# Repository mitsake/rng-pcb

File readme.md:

# CircuitPython Random Number Generator

This is my contribution to the Boldport Club's community run Board Swap Project, a hardware random number generator that uses avalanche noise to make patterns and roll dice. Apart from being part of the community project, my other motivations were interest in randomness and the processes that can be used to generate it, along with the idea of using PCBs to build an enclosure.

**Please note that I made this for fun - if you need random numbers for anything important, this isn't the project you're looking for.**

## Operation

A ST662 charge pump produces the 12 V required to reverse-bias Q1, which produces the actual randomness. When electrons travel through this junction, Q2 allows current to flow to ground. This signal is amplified by Q3, run through a voltage divider, and fed into the ADC of an ATSAMD21E18 microcontroller, which has been flashed with the [Adafruit Trinket M0][trinket] bootloader to allow programming with CircuitPython.

[trinket]: https://www.adafruit.com/product/3500

The display is an inexpensive 128 × 32 SSD1306-based OLED, and the in-built capacitive touch that's on the Trinket M0 hardware is routed to the top left (pin A3) and right (A4) corners of the top PCB to allow for input. If you don't have KiCad, you can use the [PDF schematic][schematic] - it's all pretty simple.

[schematic]: docs/schematic.pdf

## Making your own

You can use the KiCad files in the 'hardware' directory to generate gerbers and get them made at your favourite PCB fab. I had my prototypes made at [OSH Park][oshpark] (who accept the `.kicad_pcb` file directly), and once I'd finished the final design, got a 'protopack' made at [Dirty PCBs][dirtypcbs]. The gerbers are available in a [zip file][zip] which should be accepted by most fabs, and assembly instructions can be found [here][assembly]. Make sure the PCB thickness is 1.6 mm - Dirty PCBs default to 1.2 mm, which will cause clearance issues.

[oshpark]: https://www.oshpark.com/
[dirtypcbs]: https://dirtypcbs.com/store/pcbs/
[assembly]: docs/assembly.md
[zip]: hardware/gerbers/rng-pcb-dirtypcbs.zip

## Credits

This project was only possible thanks to the electrical designs, libraries, and articles written by others. Many thanks to the people below whose work was used to build this project, and to the Boldport Club Discord for the inspiration to build something and the help and support they're always happy to provide.

- Adafruit's [Trinket M0 schematic][m0schem], which I shamelessly copied for the microcontroller and its supporting components. I've also used Adafruit's bootloader (and consequently their USB VID and PID), so this project is strictly a DIY build. Please don't distribute finished versions of this project with the Adafruit bootloader installed.
- Aaron Logue's [Hardware Random Number Generator][aaronl] started me on the path towards making the project, and gave the basic circuit.
- Giorgio Vazzana's [amazing writeup][giorgiov] of his experiments with this design, including precise measurements of transistor breakdown voltages, analogue and digital output circuits, and rigorous testing of the output.
- Walter Anderson's [Google Sites][waltera] page has a lot of really interesting information on entropy, both from this design and others.
- Rob Seward's [Arduino Uno design][robs] feeds the output from the noise circuit into an ADC and uses software to produce the actual random bits, an approach I mostly copied.
- The pattern on the top PCB (`triangle_pattern.kicad_mod`) is made with Quinn Rohlf's [Trianglify][trianglify] library.
- The `mouse-bite-2mm-slot.kicad_mod` footprint comes from [this repository][madworm] by madworm.

[m0schem]: https://learn.adafruit.com/assets/45723
[aaronl]: http://www.cryogenius.com/hardware/rng/
[giorgiov]: http://holdenc.altervista.org/avalanche/index.html
[waltera]: https://sites.google.com/site/astudyofentropy/project-definition/avalanche-noise
[robs]: http://robseward.com/misc/RNG2/
[trianglify]: https://github.com/qrohlf/trianglify
[madworm]: https://github.com/madworm/Panelization.pretty

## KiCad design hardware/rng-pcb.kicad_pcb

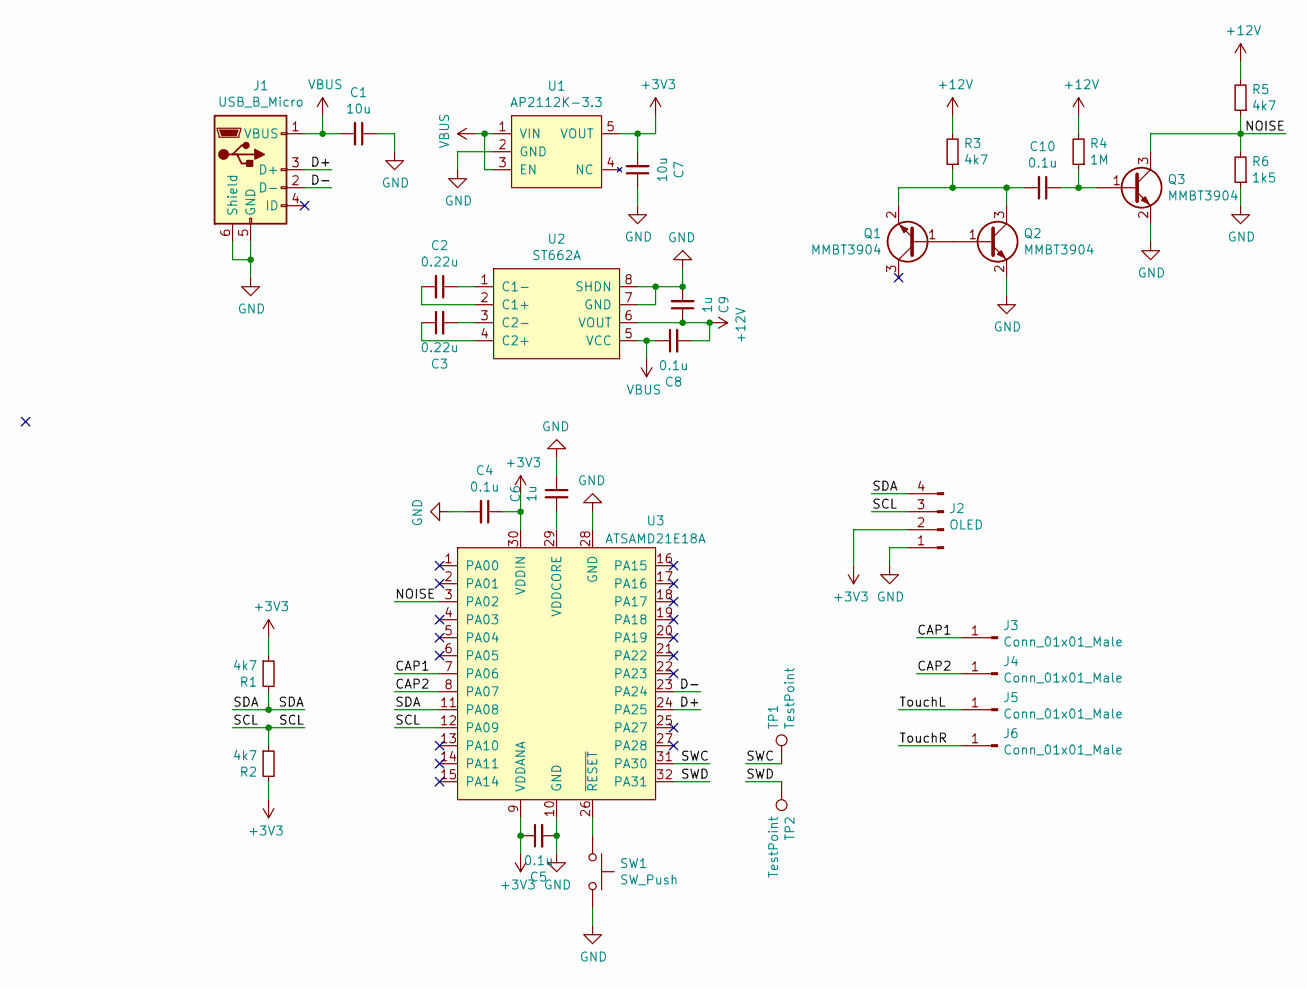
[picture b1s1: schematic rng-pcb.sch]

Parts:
C1, C7: 10u; C_0603
C2, C3: 0.22u; C_0603
C4, C5, C8, C10: 0.1u; C_0603
C6, C9: 1u; C_0603
J1: USB_B_Micro; Molex-476420001
J2: OLED; PinHeader_1x04_P2.54mm_Vertical
J3, J4, J5, J6: Conn_01x01_Male; TH_Pad
Q1, Q2, Q3: MMBT3904; SOT523
R1, R2, R3, R5: 4k7; R_0603
R4: 1M; R_0603
R6: 1k5; R_0603
SW1: SW_Push; Wurth-434331013822
TP1, TP2: TestPoint; Test_Point_Pad_d1.0mm
U1: AP2112K-3.3; TSOT-23-5
U2: ST662A; SOIC-8_3.9x4.9mm_Pitch1.27mm
U3: ATSAMD21E18A; TQFP-32_7x7mm_Pitch0.8mm

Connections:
+3V3: C4.1, C5.1, C7.2, J2.2, R1.1, R2.2, U1.5 (VOUT), U3.9 (VDDANA), U3.30 (VDDIN)
+12V: C8.2, C9.1, R3.2, R4.2, R5.2, U2.6 (VOUT)
/CAP1: J3.1, U3.7 (PA06)
/CAP2: J4.1, U3.8 (PA07)
/D+: J1.3 (D+), U3.24 (PA25)
/D-: J1.2 (D-), U3.23 (PA24)
/NOISE: Q3.3 (C), R5.1, R6.2, U3.3 (PA02)
/SCL: J2.3, R2.1, U3.12 (PA09)
/SDA: J2.4, R1.2, U3.11 (PA08)
/SWC: TP1.1, U3.31 (PA30)
/SWD: TP2.1, U3.32 (PA31)
/TouchL: J5.1
/TouchR: J6.1
GND: C1.1, C4.2, C5.2, C6.1, C7.1, C9.2, J1.5 (GND), J1.6 (Shield), J2.1, Q2.2 (E), Q3.2 (E), R6.1, SW1.2, U1.2 (GND), U2.7 (GND), U2.8 (SHDN), U3.10 (GND), U3.28 (GND)
unnamed: C2.1, U2.1 (C1-)
unnamed: C2.2, U2.2 (C1+)
unnamed: C3.1, U2.4 (C2+)
unnamed: C3.2, U2.3 (C2-)
unnamed: C6.2, U3.29 (VDDCORE)
unnamed: C10.1, Q3.1 (B), R4.1
unnamed: C10.2, Q1.2 (E), Q2.3 (C), R3.1
unnamed: Q1.1 (B), Q2.1 (B)
unnamed: SW1.1, U3.26 (~RESET)
VBUS: C1.2, C8.1, J1.1 (VBUS), U1.1 (VIN), U1.3 (EN), U2.5 (VCC)

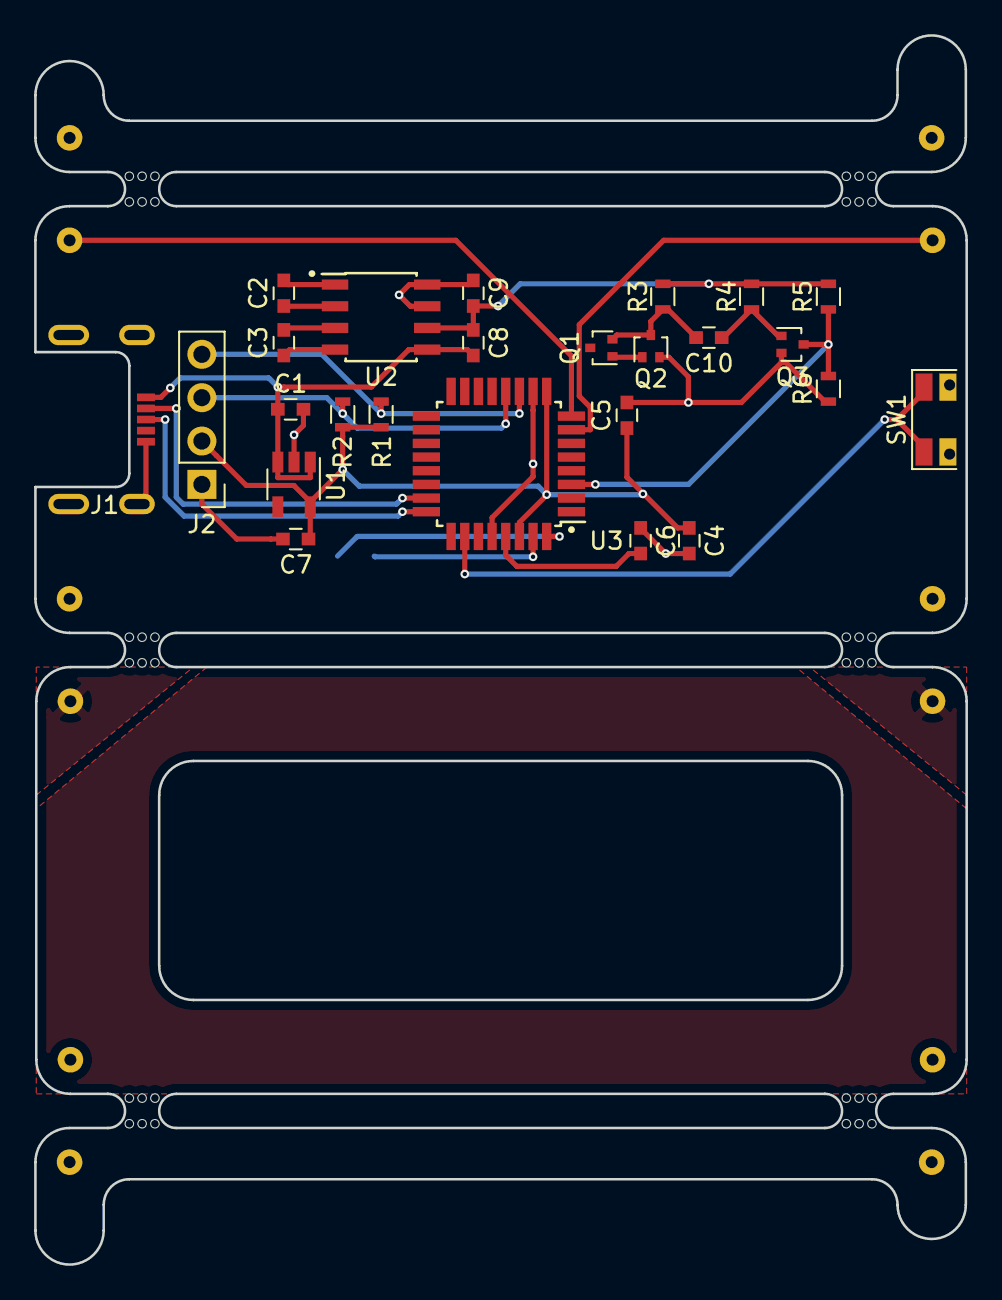
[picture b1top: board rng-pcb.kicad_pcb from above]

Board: 2 copper layers, 54.6 x 72.0 mm, 37 parts (0 on the bottom side), 22 nets.

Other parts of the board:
mouse-bite-2mm-slot, mouse-bite-2mm-slot#2, mouse-bite-2mm-slot#3, mouse-bite-2mm-slot#4, mouse-bite-2mm-slot#5, mouse-bite-2mm-slot#6: VAL**; mouse-bite-2mm-slot

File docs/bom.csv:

"Reference","Quantity","Value","Footprint","Digikey","Mouser"
"C1, C7",2,"10 μF, 16 V","0603","1276-6769-1-ND","81-GRM188C81C106MA3D"
"C2, C3",2,"0.22 μF, 16 V","0603","1276-1112-1-ND","81-GCJ188R71C224KA1D"
"C4, C5, C8, C10",4,"0.1 μF, 16 V","0603","1276-1005-1-ND","81-GCJ188R71C105KA1D"
"C6, C9",2,"1 μF, 16 V","0603","1276-6524-1-ND","81-GCM188R71C105KA4J"
"J1",1,"USB-micro jack","Molex 47642-0001","WM1398CT-ND","538-47642-0001"
"J2",1,"128 × 32 OLED","1×4 pin header","",""
"Q1, Q2, Q3",3,"MMBT3904T","SOT416 (aka SOT523)","MMBT3904T-FDICT-ND","621-MMBT3904T-F"
"R1, R2, R3, R5",4,"4.7 kΩ","0603","311-4.70KHRCT-ND","603-RC0603FR-074K7L"
"R4",1,"1 MΩ","0603","311-1.00MHRCT-ND","603-RC0603FR-071ML"
"R6",1,"1.5 kΩ","0603","311-1.50KHRCT-ND","603-RC0603FR-071K5L"
"SW1",1,"Push switch","Wurth 434331013822","732-10144-1-ND","710-434331013822"
"U1",1,"AP2112K-3.3","SOT 23-5","AP2112K-3.3TRG1DICT-ND","621-AP2112K-3.3TRG1"
"U2",1,"ST662A","SOIC-8","497-6541-1-ND","511-ST662ABD-TR"
"U3",1,"ATSAMD21E18A","TQFP-32","ATSAMD21E18A-AUTCT-ND","556-ATSAMD21E18A-AUT"

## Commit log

2019-11-18 Directory restructure and image testing
2019-11-20 Added another picture
2019-11-24 Documentation mostly complete and test files removed
2019-11-25 Finished assembly and removed old (low-quality) picture
2019-11-25 Created separate BOM
2019-11-25 Added bom.csv
2019-11-25 BOM updates, footprints changed
2019-11-25 Gitignore updates, stop tracking backup files
2019-11-29 Some decent images
2019-12-06 One more image
2019-12-06 Final images and PDF schematic added
2019-12-11 Add information on use of Adafruit bootloader
2020-05-01 added licence
2020-05-01 moving files
